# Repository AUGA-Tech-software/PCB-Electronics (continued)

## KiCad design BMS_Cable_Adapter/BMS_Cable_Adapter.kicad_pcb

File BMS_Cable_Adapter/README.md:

# BMS Cable Adapter

Adapter to simplify connection from battery cell to EMUS BMS

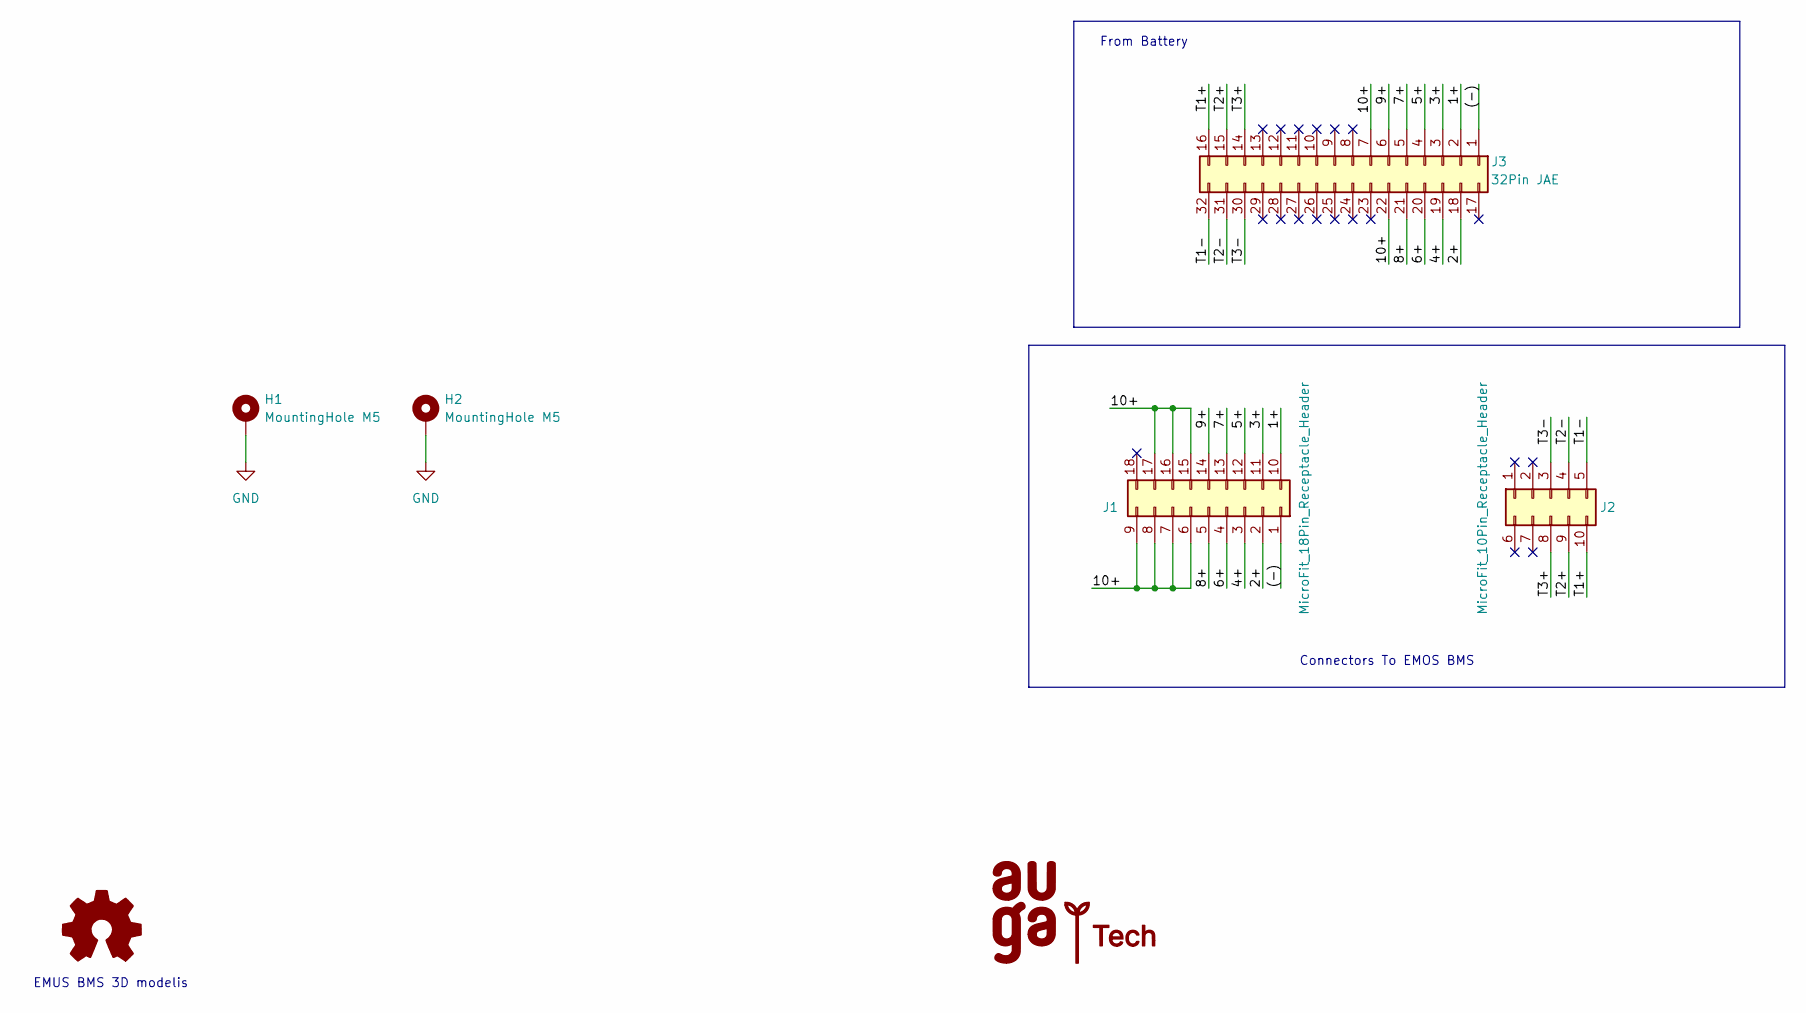
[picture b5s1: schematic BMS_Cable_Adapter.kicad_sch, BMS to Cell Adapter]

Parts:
H1, H2: MountingHole M5; MountingHole_5.3mm_M5_Pad
J1: MicroFit_18Pin_Receptacle_Header; Molex_Micro-Fit_BMI_Receptacle_18Pin_44764
J2: MicroFit_10Pin_Receptacle_Header; Molex_Micro-Fit_BMI_Receptacle_10Pin_44764
J3: 32Pin JAE; JAE_MX34032NF2
SYM1: Logo_Open_Hardware_Small; Gauge_10mm_Type3_SilkScreenTop

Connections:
/1+: J1.10, J3.2
/2+: J1.2, J3.18
/3+: J1.11, J3.3
/4+: J1.3, J3.19
/5+: J1.12, J3.4
/6+: J1.4, J3.20
/7+: J1.13, J3.5
/8+: J1.5, J3.21
/9+: J1.14, J3.6
/10+: J1.6, J1.7, J1.8, J1.9, J1.15, J1.16, J1.17, J3.7, J3.22
/(-): J1.1, J3.1
/T1+: J2.10, J3.16
/T1-: J2.5, J3.32
/T2+: J2.9, J3.15
/T2-: J2.4, J3.31
/T3+: J2.8, J3.14
/T3-: J2.3, J3.30
GND: H1.1, H2.1

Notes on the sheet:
From Battery
Connectors To EMOS BMS
EMUS BMS 3D modelis

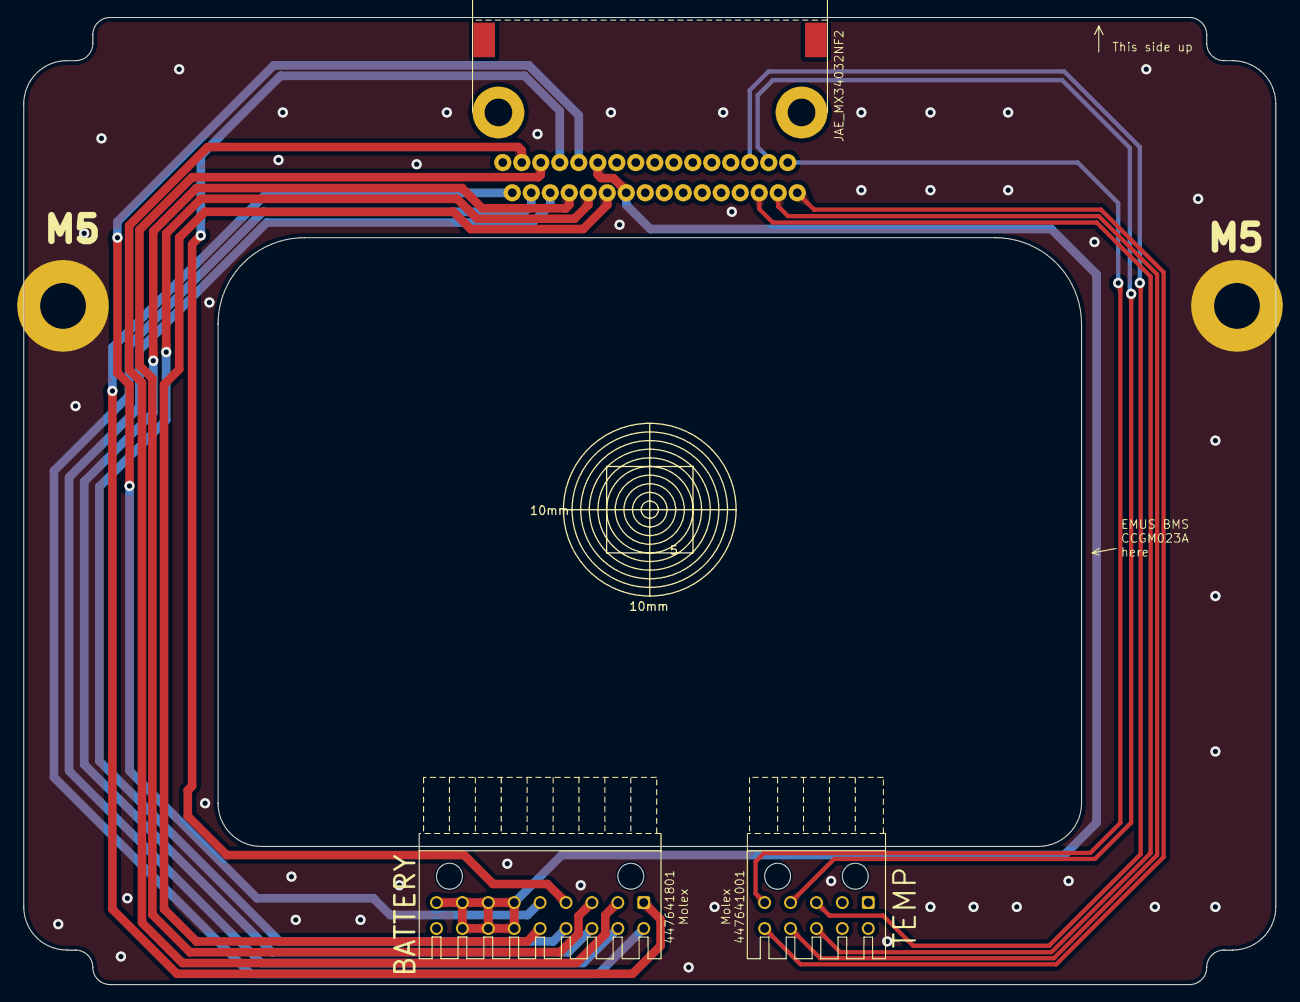
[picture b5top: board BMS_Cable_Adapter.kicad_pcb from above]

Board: 2 copper layers, 145.0 x 112.0 mm, 6 parts (0 on the bottom side), 18 nets.

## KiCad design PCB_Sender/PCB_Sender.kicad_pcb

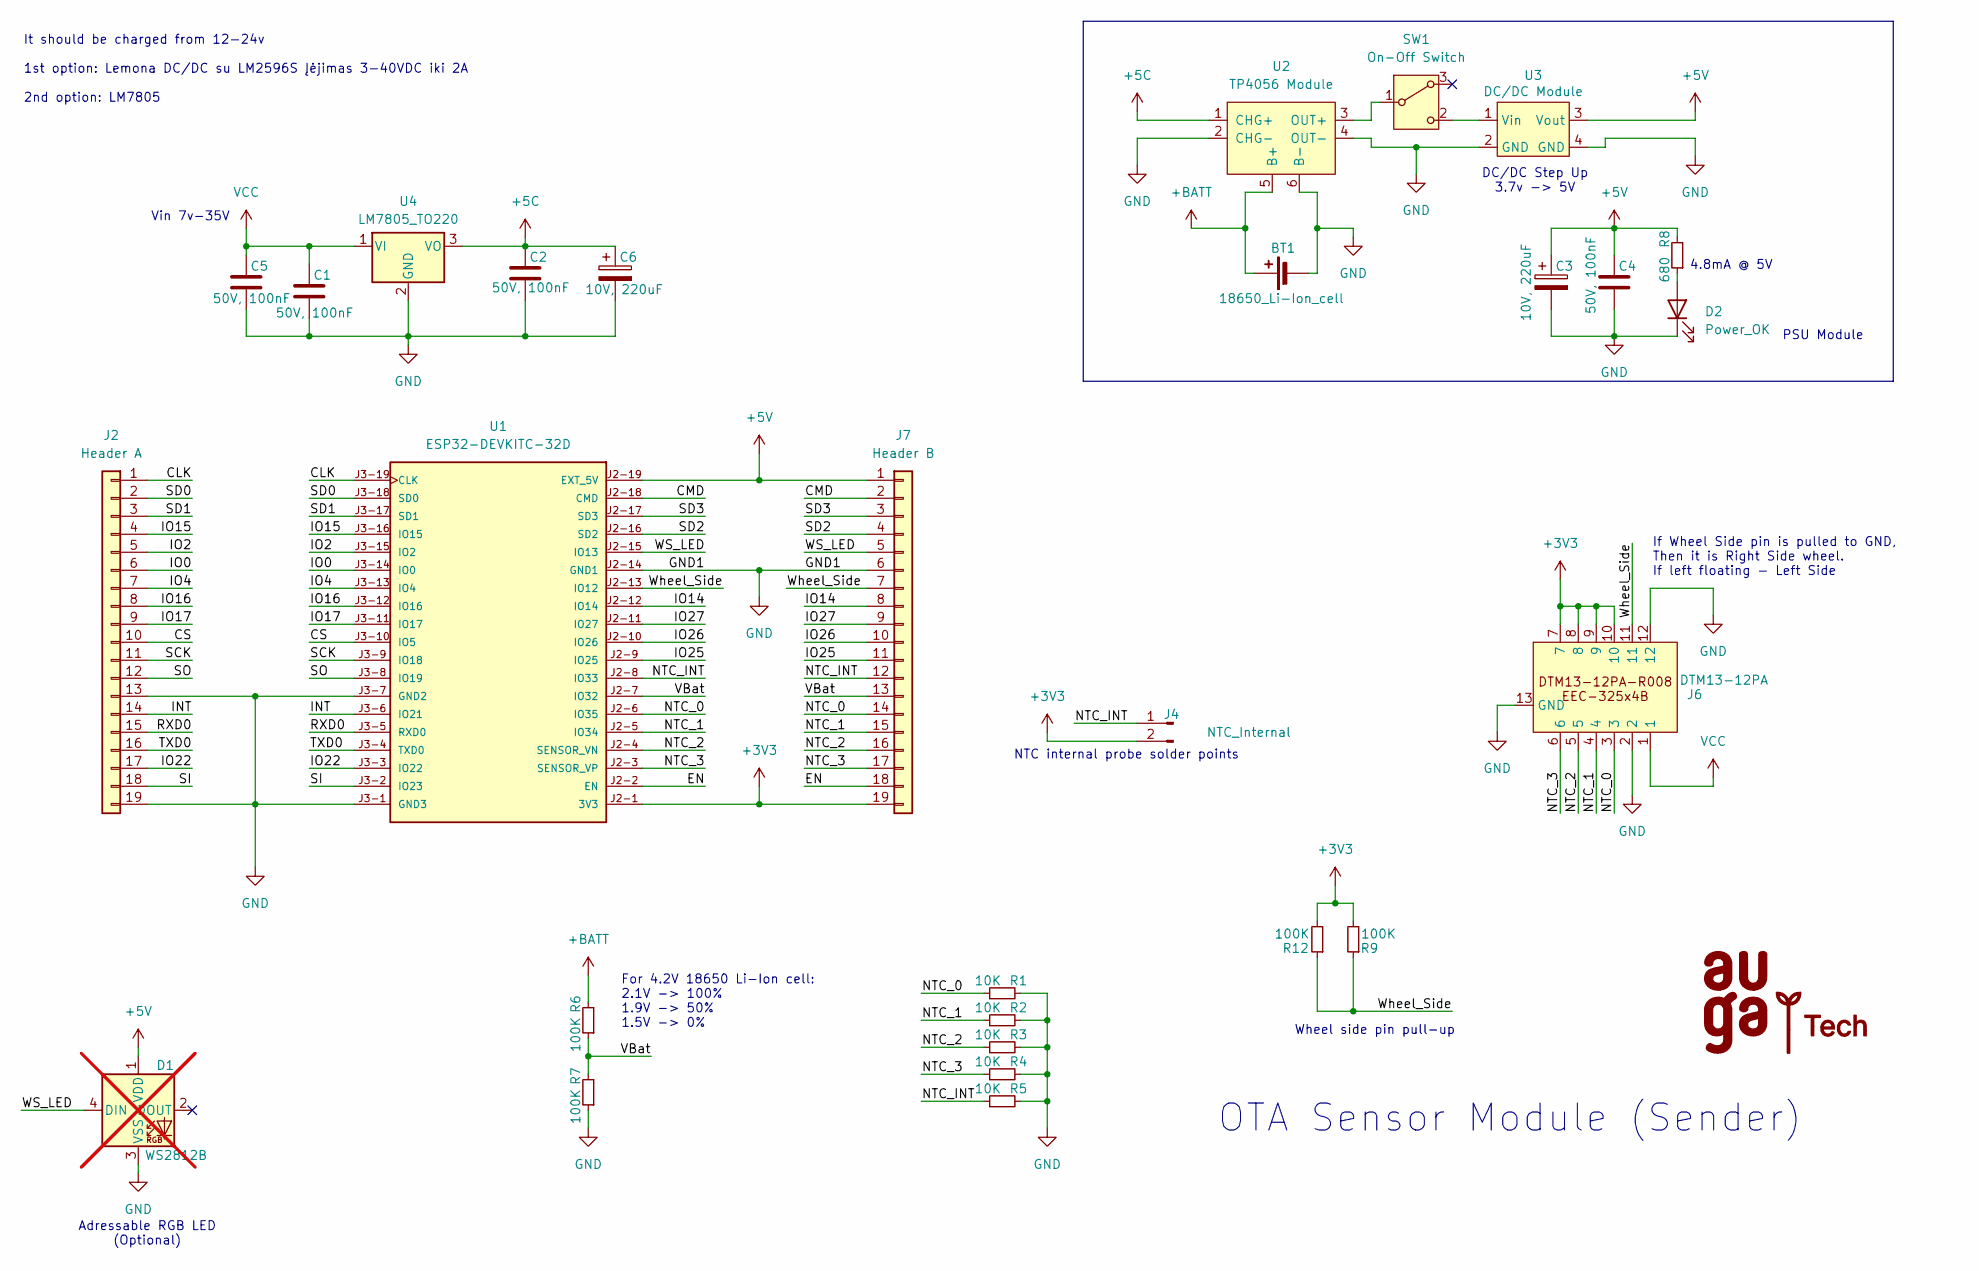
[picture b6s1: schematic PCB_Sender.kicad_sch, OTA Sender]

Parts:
BT1: 18650_Li-Ion_cell; BatteryHolder_MPD_BH-18650-PC2
C1, C2, C4, C5: 50V, 100nF; C_1206_3216Metric; JLCPCB Part # C24497
C3, C6: 10V, 220uF; CP_Radial_D6.3mm_P2.50mm
D1: WS2812B; LED_WS2812B_PLCC4_5.0x5.0mm_P3.2mm; not fitted
D2: Power_OK; LED_0805_2012Metric; JLCPCB Part # C2297
G1: AUGA-Tech-LOGO; AUGA-Tech-footprint
J2: Header A; PinHeader_1x19_P2.54mm_Vertical
J4: NTC_Internal; PinHeader_1x02_P2.54mm_Vertical
J6: DTM13-12PA; DTM13-12PA-R008
J7: Header B; PinHeader_1x19_P2.54mm_Vertical
R1, R2, R3, R4, R5: 10K; R_0805_2012Metric; JLCPCB Part # C17414
R6, R7, R9, R12: 100K; R_0805_2012Metric; JLCPCB Part # C149504
R8: 680; R_0805_2012Metric; JLCPCB Part # C17798
SW1: On-Off Switch; SW_Slide_SPDT_Straight_CK_OS102011MS2Q; MPN OS102011MS2QS1
U1: ESP32-DEVKITC-32D; MODULE_ESP32-DEVKITC-32D
U2: TP4056 Module; TP4056-Module
U3: DC/DC Module; DCDC_StepUp
U4: LM7805_TO220; TO-252-2; JLCPCB Part # C58069

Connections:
+3V3: J4.2, J6.7, J6.8, J6.9, J6.10, J7.19, R9.2, R12.2, U1.J2-1 (3V3)
+5C: C2.1, C6.1, U2.1 (CHG+), U4.3 (VO)
+5V: C3.1, C4.1, D1.1 (VDD), J7.1, R8.2, U1.J2-19 (EXT_5V), U3.3 (Vout)
+BATT: BT1.1 (+), R6.2, U2.5 (B+)
/CLK: J2.1, U1.J3-19 (CLK)
/CMD: J7.2, U1.J2-18 (CMD)
/CS: J2.10, U1.J3-10 (IO5)
/EN: J7.18, U1.J2-2 (EN)
/INT: J2.14, U1.J3-6 (IO21)
/IO0: J2.6, U1.J3-14 (IO0)
/IO2: J2.5, U1.J3-15 (IO2)
/IO4: J2.7, U1.J3-13 (IO4)
/IO14: J7.8, U1.J2-12 (IO14)
/IO15: J2.4, U1.J3-16 (IO15)
/IO16: J2.8, U1.J3-12 (IO16)
/IO17: J2.9, U1.J3-11 (IO17)
/IO22: J2.17, U1.J3-3 (IO22)
/IO25: J7.11, U1.J2-9 (IO25)
/IO26: J7.10, U1.J2-10 (IO26)
/IO27: J7.9, U1.J2-11 (IO27)
/NTC_0: J6.3, J7.14, R1.1, U1.J2-6 (IO35)
/NTC_1: J6.4, J7.15, R2.1, U1.J2-5 (IO34)
/NTC_2: J6.5, J7.16, R3.1, U1.J2-4 (SENSOR_VN)
/NTC_3: J6.6, J7.17, R4.1, U1.J2-3 (SENSOR_VP)
/NTC_INT: J4.1, J7.12, R5.1, U1.J2-8 (IO33)
/RXD0: J2.15, U1.J3-5 (RXD0)
/SCK: J2.11, U1.J3-9 (IO18)
/SD0: J2.2, U1.J3-18 (SD0)
/SD1: J2.3, U1.J3-17 (SD1)
/SD2: J7.4, U1.J2-16 (SD2)
/SD3: J7.3, U1.J2-17 (SD3)
/SI: J2.18, U1.J3-2 (IO23)
/SO: J2.12, U1.J3-8 (IO19)
/TXD0: J2.16, U1.J3-4 (TXD0)
/VBat: J7.13, R6.1, R7.2, U1.J2-7 (IO32)
/WS_LED: D1.4 (DIN), J7.5, U1.J2-15 (IO13)
/Wheel_Side: J6.11, J7.7, R9.1, R12.1, U1.J2-13 (IO12)
GND: BT1.2 (-), C1.2, C2.2, C3.2, C4.2, C5.2, C6.2, D1.3 (VSS), D2.1 (K), J2.13, J2.19, J6.2, J6.12, J6.13 (GND), J7.6, R1.2, R2.2, R3.2, R4.2, R5.2, R7.1, U1.J2-14 (GND1), U1.J3-1 (GND3), U1.J3-7 (GND2), U2.2 (CHG-), U2.4 (OUT-), U2.6 (B-), U3.2 (GND), U3.4 (GND), U4.2 (GND)
unnamed: D2.2 (A), R8.1
unnamed: SW1.1 (B), U2.3 (OUT+)
unnamed: SW1.2 (C), U3.1 (Vin)
VCC: C1.1, C5.1, J6.1, U4.1 (VI)

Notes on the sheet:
PSU Module
DC/DC Step Up 3.7v -> 5V
If Wheel Side pin is pulled to GND, Then it is Right Side wheel. If left floating - Left Side
NTC internal probe solder points
It should be charged from 12-24v 1st option: Lemona DC/DC su LM2596S Įėjimas 3-40VDC iki 2A 2nd option: LM7805
Adressable RGB LED (Optional)
Vin 7v-35V
Wheel side pin pull-up
4.8mA @ 5V
For 4.2V 18650 Li-Ion cell: 2.1V -> 100% 1.9V -> 50% 1.5V -> 0%
OTA Sensor Module (Sender)

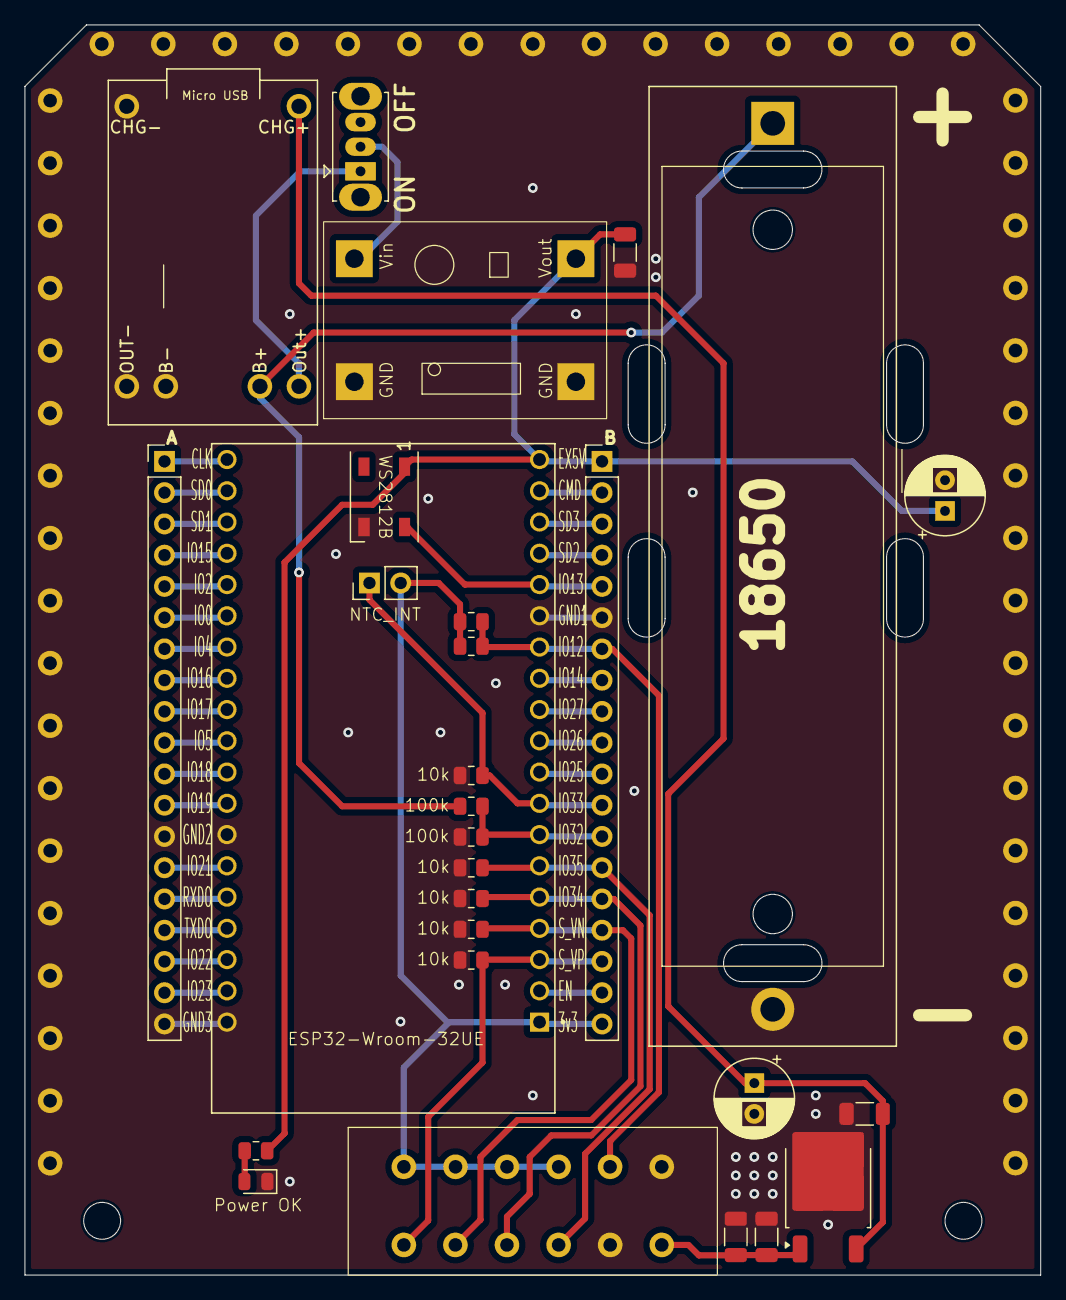
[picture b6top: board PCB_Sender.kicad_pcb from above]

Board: 2 copper layers, 82.6 x 101.6 mm, 29 parts (1 on the bottom side), 42 nets.

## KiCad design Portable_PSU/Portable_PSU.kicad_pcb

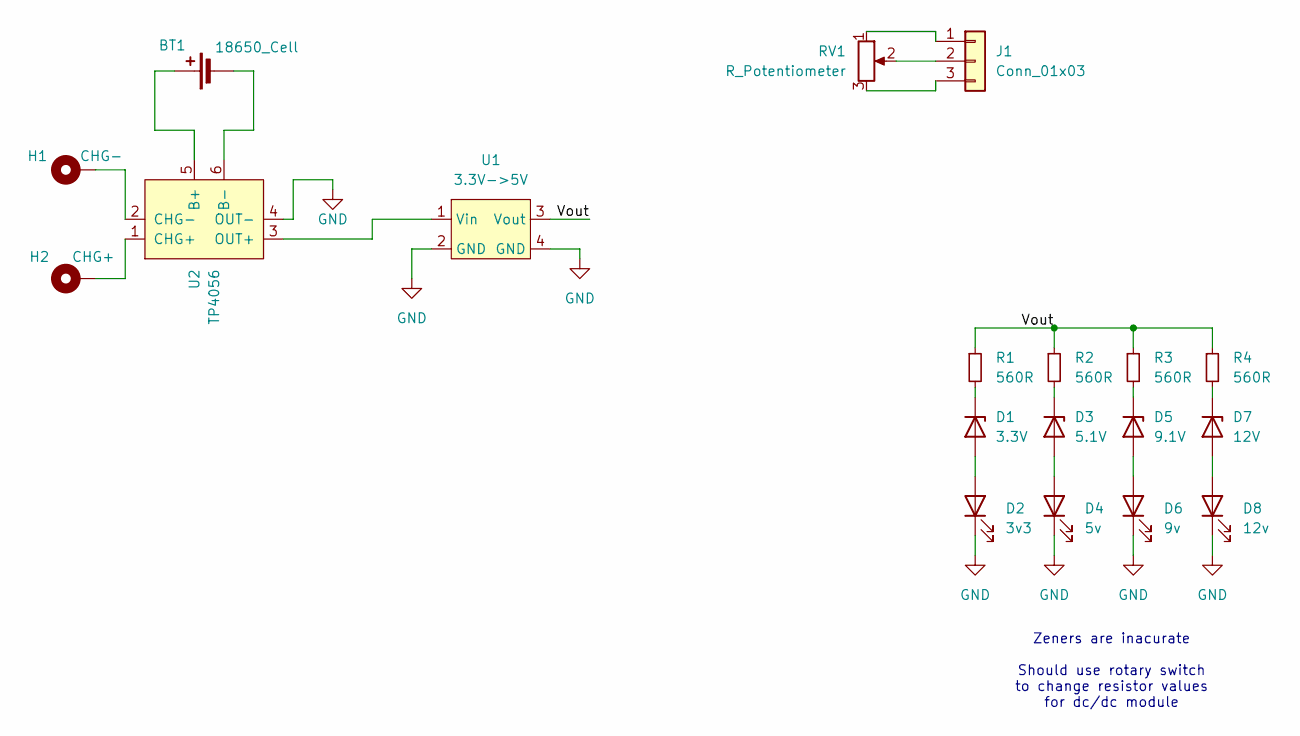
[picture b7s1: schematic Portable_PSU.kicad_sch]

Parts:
BT1: 18650_Cell; BatteryHolder_MPD_BH-18650-PC2
D1: 3.3V; D_DO-34_SOD68_P7.62mm_Horizontal
D2: 3v3; LED_0805_2012Metric
D3: 5.1V; D_DO-34_SOD68_P7.62mm_Horizontal
D4: 5v; LED_0805_2012Metric
D5: 9.1V; D_DO-34_SOD68_P7.62mm_Horizontal
D6: 9v; LED_0805_2012Metric
D7: 12V; D_DO-34_SOD68_P7.62mm_Horizontal
D8: 12v; LED_0805_2012Metric
H1: CHG-; MountingHole_3.2mm_M3_Pad
H2: CHG+; MountingHole_3.2mm_M3_Pad
J1: Conn_01x03; PinSocket_1x03_P2.54mm_Vertical
R1, R2, R3, R4: 560R; R_0805_2012Metric
RV1: R_Potentiometer; Potentiometer_Alps_RK163_Single_Horizontal
U1: 3.3V->5V; DCDC_StepUp
U2: TP4056; TP4056-Module

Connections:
/Vout: R1.1, R2.1, R3.1, R4.1, U1.3 (Vout)
GND: D2.1 (K), D4.1 (K), D6.1 (K), D8.1 (K), U1.2 (GND), U1.4 (GND), U2.4 (OUT-)
unnamed: BT1.1 (+), U2.5 (B+)
unnamed: BT1.2 (-), U2.6 (B-)
unnamed: D1.2 (A), D2.2 (A)
unnamed: D1.1 (K), R1.2
unnamed: D3.2 (A), D4.2 (A)
unnamed: D3.1 (K), R2.2
unnamed: D5.2 (A), D6.2 (A)
unnamed: D5.1 (K), R3.2
unnamed: D7.2 (A), D8.2 (A)
unnamed: D7.1 (K), R4.2
unnamed: J1.1, RV1.1
unnamed: J1.2, RV1.2
unnamed: J1.3, RV1.3
unnamed: U1.1 (Vin), U2.3 (OUT+)
unnamed: H2.1, U2.1 (CHG+)
unnamed: H1.1, U2.2 (CHG-)

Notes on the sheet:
Zeners are inacurate Should use rotary switch to change resistor values for dc/dc module

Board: 2 copper layers, 19 parts (0 on the bottom side), 18 nets, no tracks yet.

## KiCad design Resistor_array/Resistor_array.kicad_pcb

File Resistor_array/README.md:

# Resistor_array
 Inline Pull UP/DOWN resistor array x4

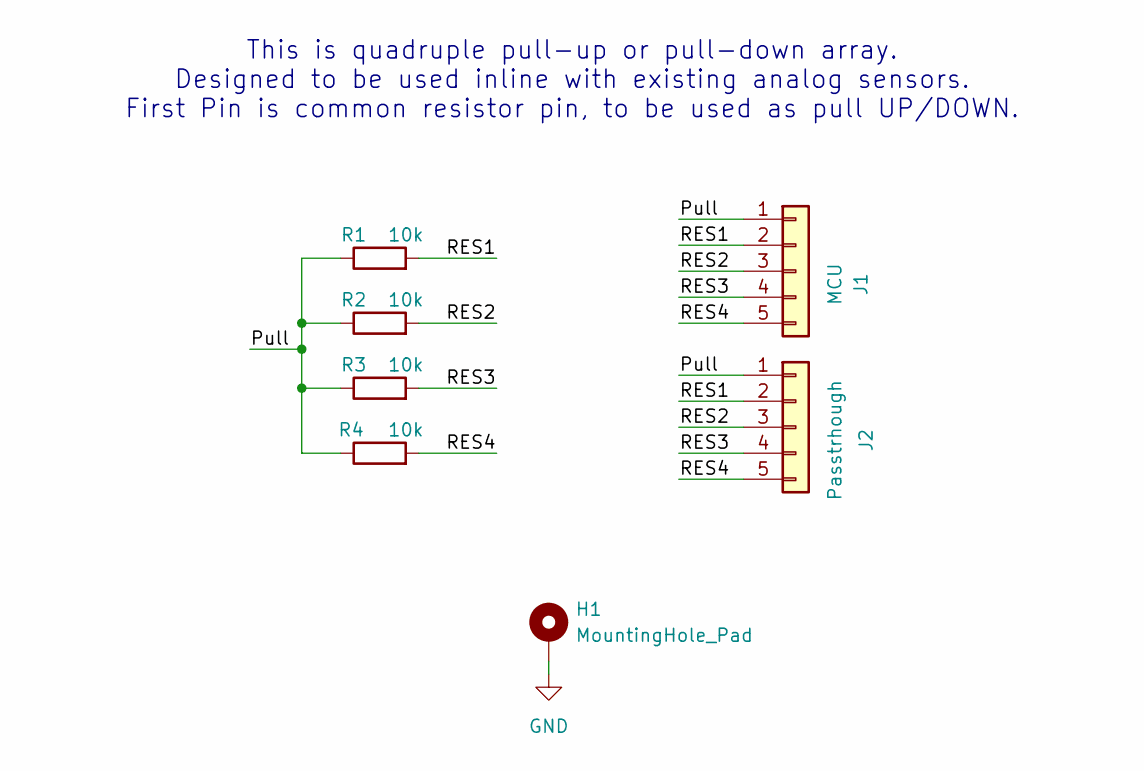
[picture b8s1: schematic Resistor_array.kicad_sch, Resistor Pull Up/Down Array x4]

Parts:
H1: MountingHole_Pad; MountingHole_4.3mm_M4_Pad
J1: MCU; TerminalBlock_bornier-5_P5.08mm
J2: Passtrhough; TerminalBlock_bornier-5_P5.08mm
R1, R2, R3, R4: 10k; R_Axial_DIN0207_L6.3mm_D2.5mm_P10.16mm_Horizontal

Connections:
/Pull: J1.1, J2.1, R1.1, R2.1, R3.1, R4.1
/RES1: J1.2, J2.2, R1.2
/RES2: J1.3, J2.3, R2.2
/RES3: J1.4, J2.4, R3.2
/RES4: J1.5, J2.5, R4.2
GND: H1.1

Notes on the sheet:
This is quadruple pull-up or pull-down array. Designed to be used inline with existing analog sensors. First Pin is common resistor pin, to be used as pull UP/DOWN.

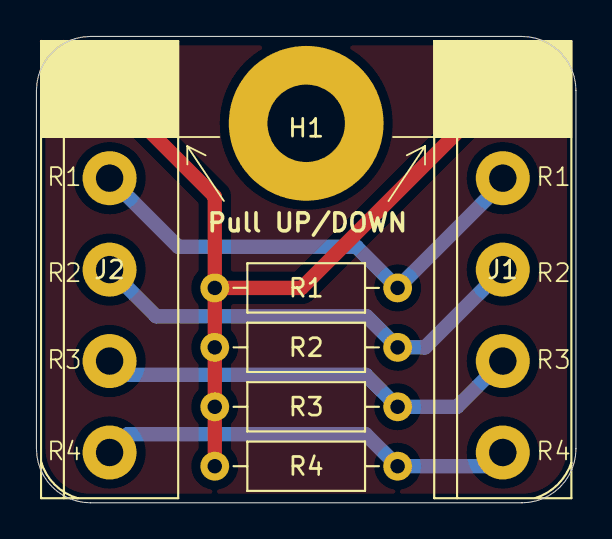
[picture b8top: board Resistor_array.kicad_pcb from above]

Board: 2 copper layers, 30.0 x 25.9 mm, 7 parts (0 on the bottom side), 5 nets.

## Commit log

2024-05-03 Added Resistor Array
2024-05-03 Added readme
2024-05-29 WiP commit
    Commited work in progress
2024-06-13 BMS Cable adapter done
    Also libraries updated
2024-07-31 PCB updates
2024-08-02 Temp Cluster update
2024-08-29 Service can connector Rev B
    Also added molex 10 pin connector 3d model
2025-02-18 Generic Update
    Just an usual commit
